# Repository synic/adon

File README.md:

adon
====

AVR Simon Clone

This is a simon clone written for AVR, specifically the ATTiny84a.  The schematic board in eagle/ has been designed to run off of 2 AA batteries, and the chip fuses in fuses.txt set the attiny84a to have a clock of 4mhz, and to have a brown out of 1.8 volts, meaning the batteries should last quite a while before they need to be replaced.

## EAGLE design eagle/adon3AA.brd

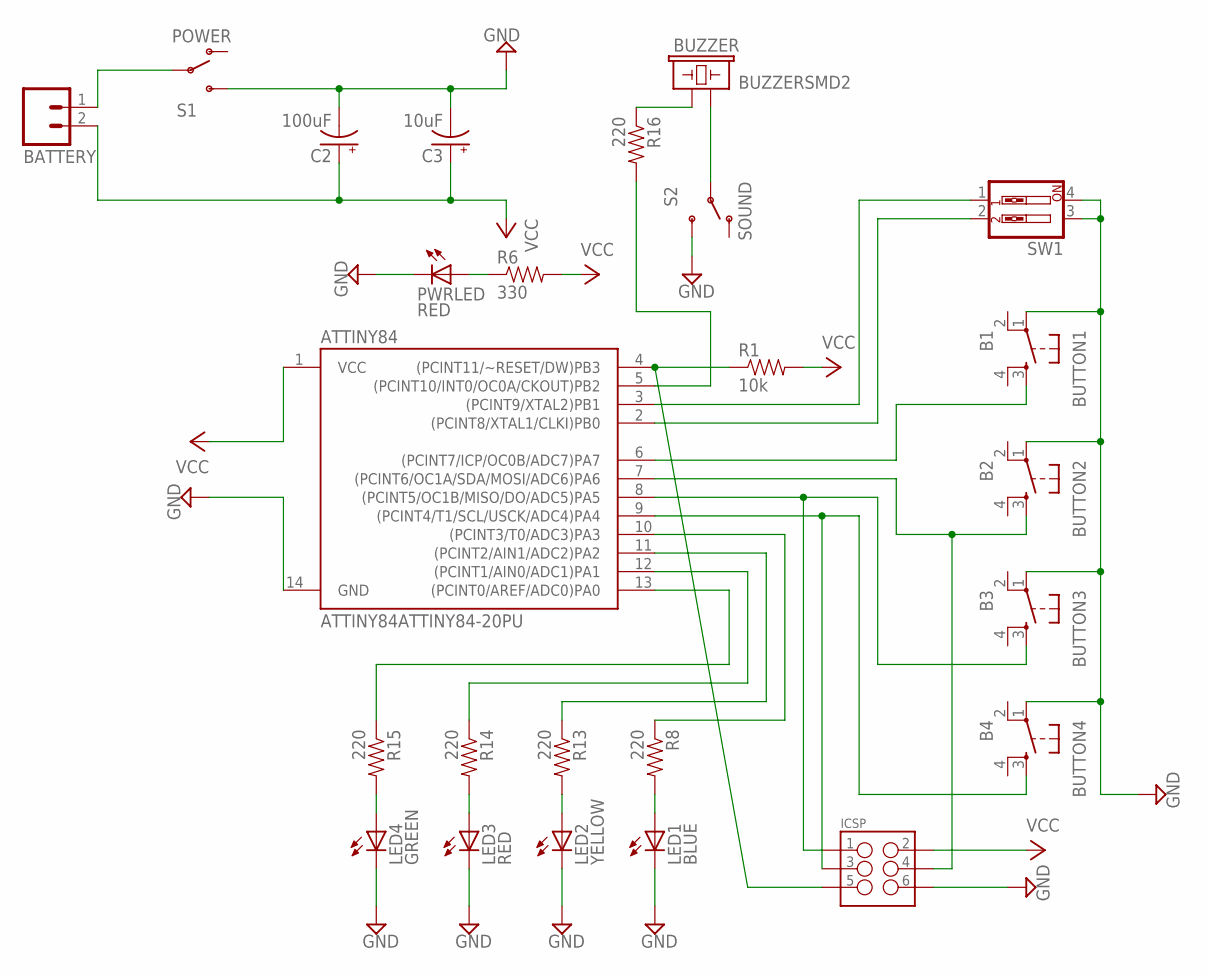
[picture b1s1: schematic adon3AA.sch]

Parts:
ATTINY84: ATTINY84ATTINY84-20PU; DIL14
BATTERY: M02JST-PTH-2; JST-2-PTH
BUTTON1: B1; TACTILE-PTH
BUTTON2: B2; TACTILE-PTH
BUTTON3: B3; TACTILE-PTH
BUTTON4: B4; TACTILE-PTH
BUZZER: BUZZERSMD2; BUZZER-CCV
C2: 100uF; CPOL-RADIAL-100UF-25V
C3: 10uF; CPOL-RADIAL-10UF-25V
ICSP: M03X2NO_SILK; 2X3-NS
LED1: BLUE; LED5MM
LED2: YELLOW; LED5MM
LED3: RED; LED5MM
LED4: GREEN; LED5MM
PWRLED: RED; LED3MM
R1: 10k; AXIAL-0.4
R6: 330; AXIAL-0.4
R8, R13, R14, R15, R16: 220; AXIAL-0.4
S1: POWER; SWITCH-SPDT_LOCK.007S
S2: SOUND; SWITCH-SPDT_LOCK.007S
SW1: SW_DIP-2; EDG-02

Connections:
GND: ATTINY84.14 (GND), BUTTON1.1, BUTTON2.1, BUTTON3.1, BUTTON4.1, C2.2 (-), C3.2 (-), ICSP.6, LED1.K (C), LED2.K (C), LED3.K (C), LED4.K (C), PWRLED.K (C), S1.3 (S), S2.3 (S), SW1.3, SW1.4
unnamed: BUZZER.+ (1), R16.P$1 (1)
unnamed: PWRLED.A, R6.P$1 (1)
unnamed: LED1.A, R8.P$2 (2)
unnamed: LED2.A, R13.P$2 (2)
unnamed: ATTINY84.6 ((PCINT7/ICP/OC0B/ADC7)PA7), BUTTON1.3
unnamed: ATTINY84.5 ((PCINT10/INT0/OC0A/CKOUT)PB2), R16.P$2 (2)
unnamed: LED3.A, R14.P$2 (2)
unnamed: LED4.A, R15.P$2 (2)
unnamed: ATTINY84.7 ((PCINT6/OC1A/SDA/MOSI/ADC6)PA6), BUTTON2.3, ICSP.4
unnamed: ATTINY84.3 ((PCINT9/XTAL2)PB1), SW1.1
unnamed: ATTINY84.2 ((PCINT8/XTAL1/CLKI)PB0), SW1.2
unnamed: BATTERY.1, S1.2
unnamed: ATTINY84.8 ((PCINT5/OC1B/MISO/DO/ADC5)PA5), BUTTON3.3, ICSP.1
unnamed: ATTINY84.9 ((PCINT4/T1/SCL/USCK/ADC4)PA4), BUTTON4.3, ICSP.3
unnamed: ATTINY84.10 ((PCINT3/T0/ADC3)PA3), R8.P$1 (1)
unnamed: ATTINY84.11 ((PCINT2/AIN1/ADC2)PA2), R13.P$1 (1)
unnamed: ATTINY84.12 ((PCINT1/AIN0/ADC1)PA1), R14.P$1 (1)
unnamed: ATTINY84.13 ((PCINT0/AREF/ADC0)PA0), R15.P$1 (1)
unnamed: ATTINY84.4 ((PCINT11/~RESET/DW)PB3), ICSP.5, R1.P$1 (1)
unnamed: BUZZER.- (2), S2.2
VCC: ATTINY84.1 (VCC), BATTERY.2, C2.1 (+), C3.1 (+), ICSP.2, R1.P$2 (2), R6.P$2 (2)

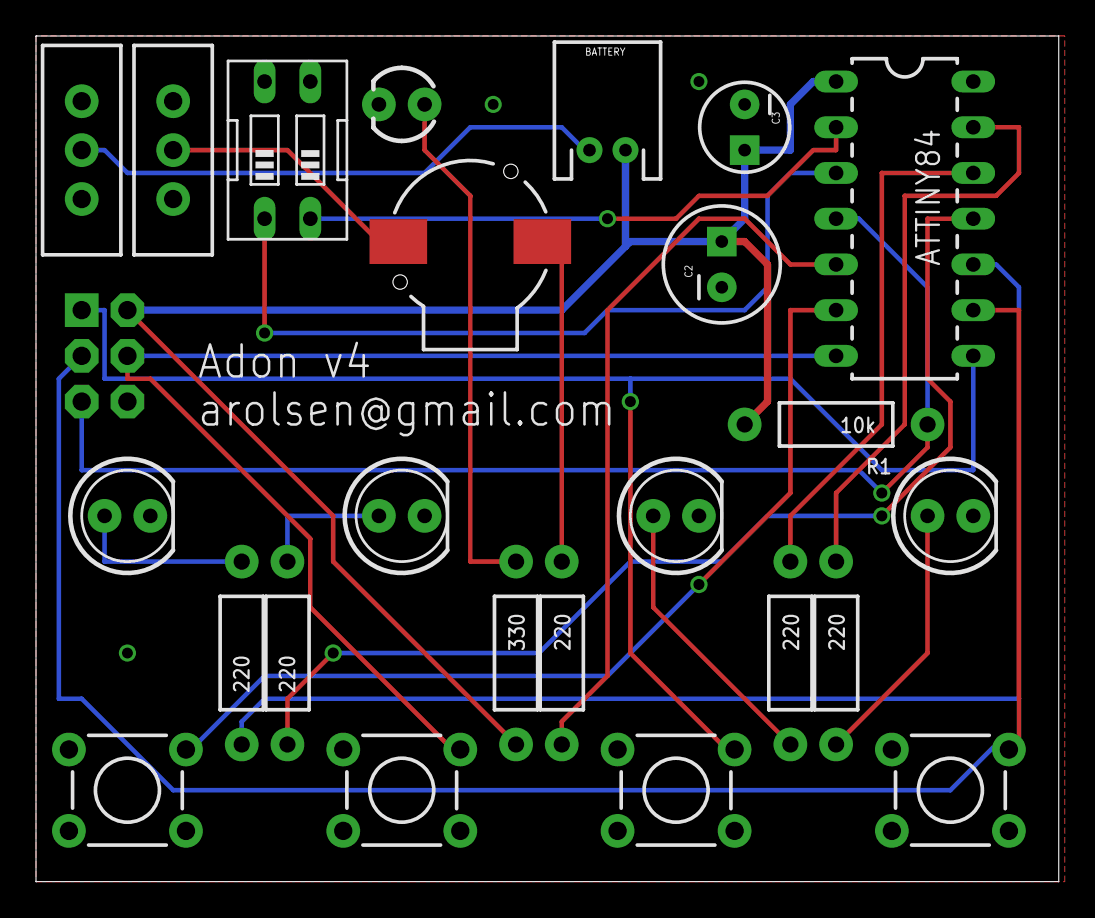
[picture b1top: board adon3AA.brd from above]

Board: 2 copper layers, 56.8 x 47.0 mm, 25 parts (0 on the bottom side), 22 nets.

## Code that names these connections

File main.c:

/*
 Application Name: Adon
 Description: A simon clone
 Author: Adam Olsen
 Email: arolsen@gmail.com
 Date: Jan 14, 2014
 Version: 0.5
 License: Apache v2

 This is written for the Amtel ATtiny84a chip.  A schematic and a board for this 
 can be found in eagle/ directory.
*/

#define F_CPU 1000000UL
#include <avr/eeprom.h>
#include <avr/io.h>
#include <util/delay.h>
#include <stdlib.h>

// musical notes
#define NOTE_E3 165
#define NOTE_CS3 139
#define NOTE_A3 220
#define NOTE_E2 82
#define NOTE_C3 131
#define NOTE_A5 880

// define led pins
#define LED1 PA3
#define LED2 PA2
#define LED3 PA1
#define LED4 PA0

// define button pins
#define BUTTON1 PA7
#define BUTTON2 PA6
#define BUTTON3 PA5
#define BUTTON4 PA4

// game mode DIP switch
#define GAMEMODE1 PB1
#define GAMEMODE2 PB0

// various game constants
#define ERROR_TONE NOTE_C3
#define WON_TONE NOTE_A5
#define MAX_LEVELS 20
#define NEXT_GAME_PAUSE_DURATION 800
#define INCREASE_SPEED_LEVELS 3
#define INCREASE_SPEED_AMOUNT 20
#define PAUSE_DURATION 200
#define INITIAL_TONE_DURATION 500
#define MAX_SPEED 200
#define MAX_LOOPS 200000UL / 8

const unsigned int TONES_FOR_BUTTON[5] = {NOTE_E3, NOTE_CS3, NOTE_A3, NOTE_E2,
    NOTE_A3};
const uint8_t LEDS[4] = {LED1, LED2, LED3, LED4};
const uint8_t BUTTONS[4] = {BUTTON1, BUTTON2, BUTTON3, BUTTON4};

uint8_t game_mode;
int button_pressed;
uint8_t level_sequence[10];
uint8_t level;
uint8_t input_mode;
unsigned long loop_count;
uint8_t current_step;
unsigned int tone_duration;
unsigned int randint;

void delay(long millis);
void no_tone(void);
void tone(int frequency, long delay);
void led_on(uint8_t led);
void led_off(uint8_t led);
void setup_gamemode(void);
void setup_level(void);
void reset_game(void);
void game_over(void);
void game_won(void);
void button_press(uint8_t index);
void button_release(uint8_t index);
void check_button_press(uint8_t index);

int main(void) {
    // do initial set up of the timer - set it up to toggle OC0A output (which
    // is PB2), and set it to ctc mode.
    TCCR0A = _BV(WGM01) | _BV(COM0A0);   

    // set PB2 as an output
    DDRB = _BV(PB2); 

    // set LED pins as outputs
    DDRA = _BV(LED1) | _BV(LED2) | _BV(LED3) | _BV(LED4);
    
    // enable pullup resistors on the button pins
    PORTA |= _BV(BUTTON1) | _BV(BUTTON2) | _BV(BUTTON3) | _BV(BUTTON4);

    // enable pullup resistors on the game mode dip switches
    PORTB |= _BV(GAMEMODE1) | _BV(GAMEMODE2);

    // get a random number to seed with
    srand(eeprom_read_word(&randint));

    // write the random seed number for next time ;-)
    eeprom_write_word(&randint, rand());

    // initialize variables
    level = 1;
    game_mode = 0;
    input_mode = 0;
    current_step = -1;
    tone_duration = INITIAL_TONE_DURATION;
    button_pressed = -1;

    delay(2000); // delay 2 seconds before starting the game.

    // loop forever
    while(1) { 
        if(!input_mode) {
            setup_level();
            input_mode = 1;
        }
        else {
            // check for button presses
            for(uint8_t i = 0; i < 4; i++) {
                check_button_press(i);
            }

            if(loop_count > MAX_LOOPS) {
                game_over();
            }

            loop_count++;
        }
    }
}

void delay(long millis) {
    for(long i = 0; i < millis; i++) _delay_ms(1);
}

void no_tone(void) {
    PORTB &= ~_BV(PB2);
    TCCR0B = 0x00;                       // turn timer off completely
}

void tone(int frequency, long delay_millis) {
    OCR0A = ((F_CPU / 64.0) / (frequency * 2.0)) - 1;
    TCCR0B = _BV(CS01) | _BV(CS00);      // set prescaler to 64

    if(delay_millis > -1) {
        delay(delay_millis);
        no_tone();
    }
}

void led_on(uint8_t led) {
    PORTA |= _BV(led);
}

void led_off(uint8_t led) {
    PORTA &= ~_BV(led);
}

/*
 * Checks the game mode dip switch, and sets the game type accordingly.  There
 * are four different game modes:
 *
 * 1. Progressing steps, not increasing speed (easy, PB0 and PB1 off)
 * 2  Progressing steps, increasing speed (medium, PB0 on PB1 off)
 * 3. Random steps, not increasing speed (hard, PB0 off and PB1 on)
 * 4. Random steps, increasing speed (super hard, PB0 and PB1 on)
 */
void setup_gamemode(void) {
    if(!bit_is_clear(PINB, PB0) && !bit_is_clear(PINB, PB1)) 
        game_mode = 0;
    else if(bit_is_clear(PINB, PB0) && !bit_is_clear(PINB, PB1)) 
        game_mode = 1;
    else if(!bit_is_clear(PINB, PB0) && bit_is_clear(PINB, PB1))
        game_mode = 2;
    else if(bit_is_clear(PINB, PB0) && bit_is_clear(PINB, PB1)) 
        game_mode = 3;
    else
        game_mode = 0;
}

/**
 * Sets up the level based on the game mode.
 */
void setup_level(void) {
    loop_count = 0;
    setup_gamemode();

    uint8_t increase_speed = (game_mode == 1 || game_mode == 3);

    if(increase_speed && level % INCREASE_SPEED_LEVELS == 0) {
        int mult = level / INCREASE_SPEED_LEVELS;
        tone_duration -= INCREASE_SPEED_AMOUNT * mult;
        if(tone_duration < MAX_SPEED) {
            tone_duration = MAX_SPEED;
        }
    }

    current_step = -1;
    uint8_t start_sequence = 0;
    if(game_mode < 2) {
        start_sequence = level - 1;
    }

    for(uint8_t i = 0; i < level; i++) {
        uint8_t step;

        if(start_sequence > 0 && game_mode < 2) {
            if(start_sequence == i) {
                step = rand() % 4;
            }
            else {
                step = level_sequence[i];
            }
        }
        else {
            step = rand() % 4;
        }

        level_sequence[i] = step;
        led_on(LEDS[step]);
        tone(TONES_FOR_BUTTON[step], tone_duration);
        led_off(LEDS[step]);
        delay(PAUSE_DURATION);
    }
}

/**
 * Reset in game variables
 */
void reset_game(void) {
    tone_duration = INITIAL_TONE_DURATION;
    level = 1;
    input_mode = 0;
    loop_count = 0;
}

void game_over(void) {
    reset_game();
    for(uint8_t i = 0; i < 4; i++) {
        led_on(LEDS[i]);
    }
    tone(ERROR_TONE, 1000);
    delay(NEXT_GAME_PAUSE_DURATION * 2);
    for(uint8_t i = 0; i < 4; i++) {
        led_off(LEDS[i]);
    }
    delay(NEXT_GAME_PAUSE_DURATION * 2);
}

void game_won(void) {
    reset_game();
    delay(200);
    for(uint8_t i = 0; i < 8; i++) {
        for(uint8_t a = 0; a < 4; a++) {
            led_on(LEDS[a]);
            tone(WON_TONE, 100);
            delay(50);
            led_off(LEDS[a]);
        }
    }

    delay(NEXT_GAME_PAUSE_DURATION);
}

void button_press(uint8_t index) {
    // turn LED on for this button
    led_on(LEDS[index]);

    // play tone for this button
    tone(TONES_FOR_BUTTON[index], -1);
}

void button_release(uint8_t index) {
    // turn LED off for this button
    led_off(LEDS[index]);

    // turn tone off for this button
    no_tone();
    
    current_step += 1;
    if(index != level_sequence[current_step]) {
        game_over();
        return;
    }

    if(current_step + 1 >= level) {
        input_mode = 0;
        level ++;

        if(level > MAX_LEVELS) {
            game_won();
            return;
        }

        delay(NEXT_GAME_PAUSE_DURATION);
    }
}

/*
 * Check button press, with debounce. Works great with the COM-00097 buttons
 * from SparkFun
 */
void check_button_press(uint8_t index) {
    if(bit_is_clear(PINA, BUTTONS[index])) {
        if(button_pressed > -1) return;

        delay(50);
        if(bit_is_clear(PINA, BUTTONS[index])) {
            button_pressed = index;
            button_press(index);
        }
    }
    
    if(button_pressed == index && 
        !bit_is_clear(PINA, BUTTONS[index])) {
        delay(50);
        if(!bit_is_clear(PINA, BUTTONS[index])) {
            button_pressed = -1;
            button_release(index);
        }
    }
}

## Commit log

2014-01-17 repo initial
2014-01-17 updated gitignore
2014-01-17 add eagle files
2014-01-17 comments
2014-01-19 woot
2014-01-20 add a 2 second delay after the game turns on to start playing
2014-01-20 add fuse support to Makefile
2014-01-23 done
2014-01-23 hopefully changes for 1mhz
2014-01-23 change bod to 2.7
2014-01-23 woot, got it down to 1mhz by setting prescaler to 64 instead of 1024
2014-01-23 these fuses are for attiny84a, not attiny84
2014-01-23 add the arduino version
2014-01-24 new board files
2014-01-24 add 3aa schematic and board
2014-01-26 board design is done
2014-01-27 add kicad files
2014-02-02 switch to avr dragon
2014-02-05 remove kicad stuff
2014-04-11 started on stm32 version
2014-04-11 stuff
2014-04-11 added old reference source
2014-04-11 delay function works now
2014-04-11 random number generator is working
2014-04-11 welp the simon part of it works!
2014-04-11 well hell, even the failed works
2014-04-11 even better
2014-04-12 it works. except for sound. boo.
2014-04-14 switch to timer 3
2014-04-26 better?
2014-04-26 sounds are done
2014-05-12 moved kicad dir to here
2014-05-12 modified gitignore
2014-05-18 change random rules
2014-05-18 fixed rand some more
2014-05-19 plz fix
2014-05-19 this seems to work even better for some reason:

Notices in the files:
parts and their libraries:
SparkFun-LED: Licensing: CC v3.0 Share-Alike You are welcome to use this library for commercial purposes.
